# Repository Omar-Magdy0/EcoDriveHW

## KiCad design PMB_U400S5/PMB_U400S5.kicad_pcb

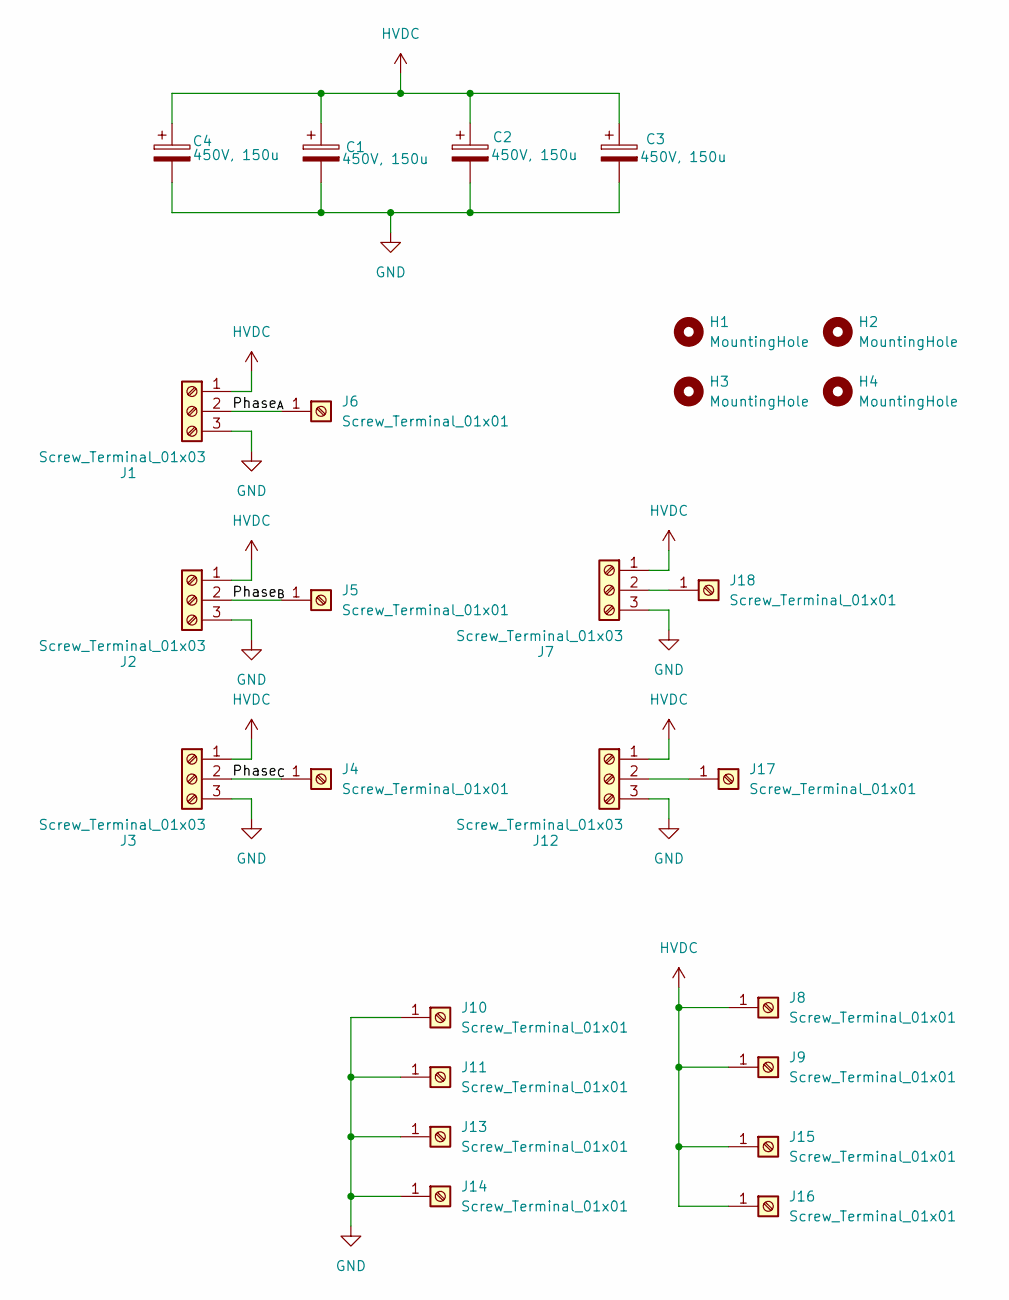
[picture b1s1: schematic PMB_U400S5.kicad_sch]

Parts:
C1, C2, C3, C4: 450V, 150u; CP_Radial_D22.0mm_P10.00mm_SnapIn_Ceye
H1, H2, H3, H4: MountingHole; MountingHole_5.3mm_M5_DIN965
J1, J2, J3, J7, J12: Screw_Terminal_01x03; SPACER_M3_PCONN_2x03
J4, J5, J6, J8, J9, J10, J11, J13, J14, J15, J16, J17, J18: Screw_Terminal_01x01; M3_PCONN_1x01

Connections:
/Phase_{A}: J1.2, J6.1 (Pin_1_1)
/Phase_{B}: J2.2, J5.1 (Pin_1_1)
/Phase_{C}: J3.2, J4.1 (Pin_1_1)
GND: C1.2, C2.2, C3.2, C4.2, J1.3, J2.3, J3.3, J7.3, J10.1 (Pin_1_1), J11.1 (Pin_1_1), J12.3, J13.1 (Pin_1_1), J14.1 (Pin_1_1)
HVDC: C1.1, C2.1, C3.1, C4.1, J1.1, J2.1, J3.1, J7.1, J8.1 (Pin_1_1), J9.1 (Pin_1_1), J12.1, J15.1 (Pin_1_1), J16.1 (Pin_1_1)
unnamed: J12.2, J17.1 (Pin_1_1)
unnamed: J7.2, J18.1 (Pin_1_1)

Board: 2 copper layers, 26 parts (0 on the bottom side), 7 nets, no tracks yet.
